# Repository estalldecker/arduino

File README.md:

# arduino
Playing with Arduino platform

Created with [KiCad](http://www.kicad-pcb.org/display/KICAD/KiCad+EDA+Software+Suite) BUILD: (25-Oct-2014 BZR 4029)-stable running in Kubuntu 15.04.

The idea is to implement side turn signals to be used in a bike. We're using for this:
 - 13 leds
 - ATMEGA328P microcontroller 
 - 9 resistors
 - 2 capacitors

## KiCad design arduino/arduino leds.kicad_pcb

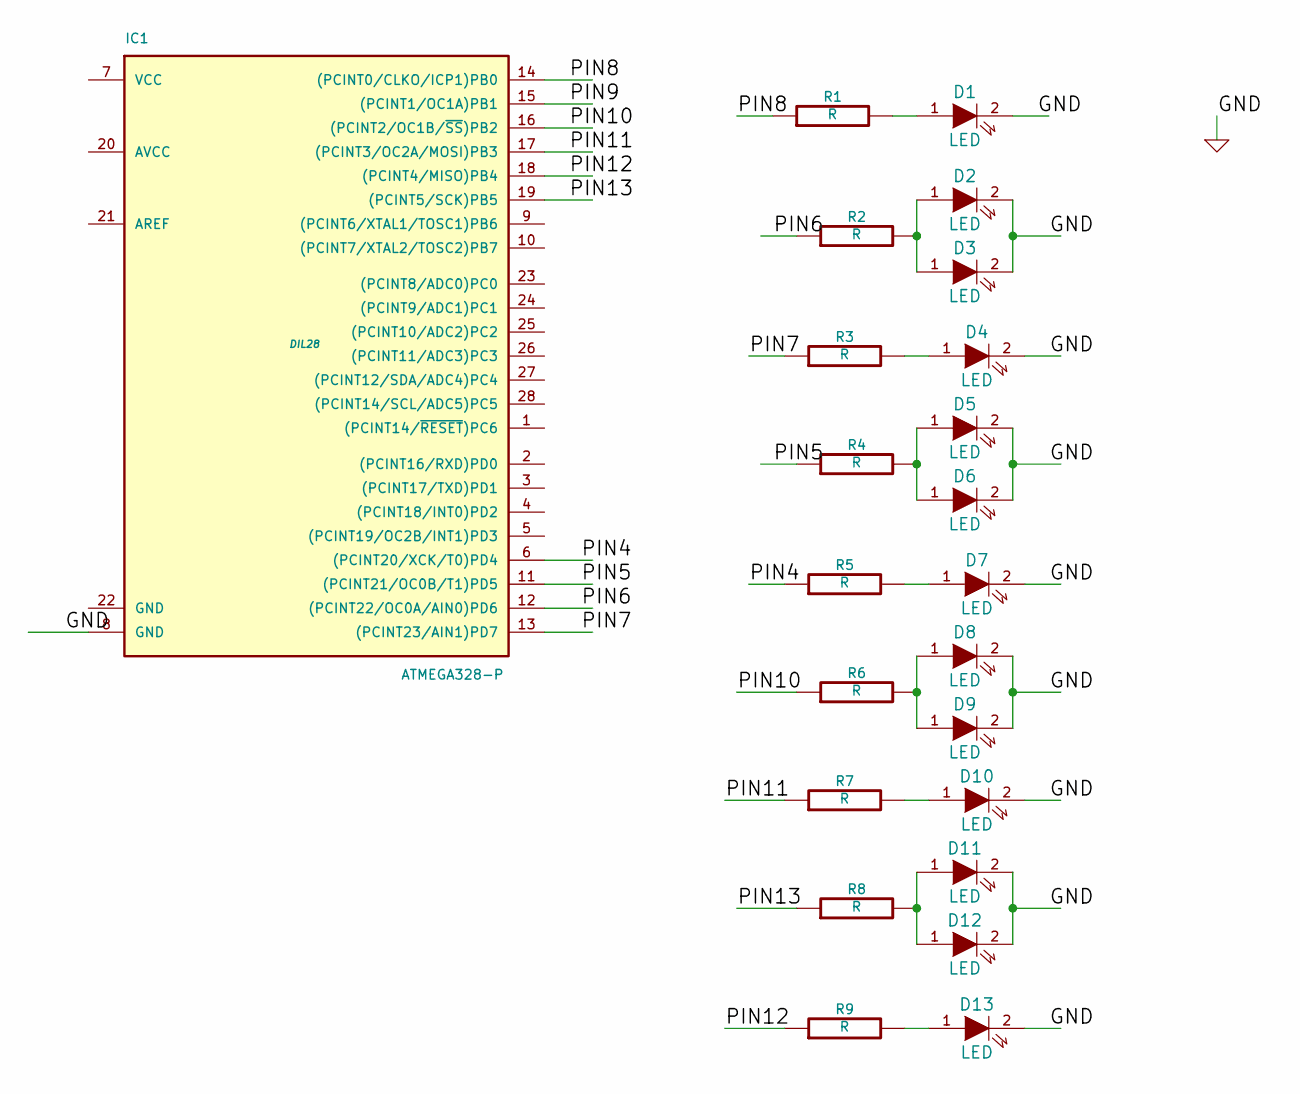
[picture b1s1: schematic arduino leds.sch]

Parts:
D1, D2, D3, D4, D5, D6, D7, D8, D9, D10, D11, D12, D13: LED
IC1: ATMEGA328-P; DIL28
R1, R2, R3, R4, R5, R6, R7, R8, R9: R

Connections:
/PIN4: IC1.6 ((PCINT20/XCK/T0)PD4), R5.1
/PIN5: IC1.11 ((PCINT21/OC0B/T1)PD5), R4.1
/PIN6: IC1.12 ((PCINT22/OC0A/AIN0)PD6), R2.1
/PIN7: IC1.13 ((PCINT23/AIN1)PD7), R3.1
/PIN8: IC1.14 ((PCINT0/CLKO/ICP1)PB0), R1.1
/PIN10: IC1.16 ((PCINT2/OC1B/~SS~)PB2), R6.1
/PIN11: IC1.17 ((PCINT3/OC2A/MOSI)PB3), R7.1
/PIN12: IC1.18 ((PCINT4/MISO)PB4), R9.1
/PIN13: IC1.19 ((PCINT5/SCK)PB5), R8.1
GND: D1.2 (K), D2.2 (K), D3.2 (K), D4.2 (K), D5.2 (K), D6.2 (K), D7.2 (K), D8.2 (K), D9.2 (K), D10.2 (K), D11.2 (K), D12.2 (K), D13.2 (K), IC1.8 (GND)
unnamed: D13.1 (A), R9.2
unnamed: D1.1 (A), R1.2
unnamed: D8.1 (A), D9.1 (A), R6.2
unnamed: D10.1 (A), R7.2
unnamed: D11.1 (A), D12.1 (A), R8.2
unnamed: D4.1 (A), R3.2
unnamed: D7.1 (A), R5.2
unnamed: D5.1 (A), D6.1 (A), R4.2
unnamed: D2.1 (A), D3.1 (A), R2.2

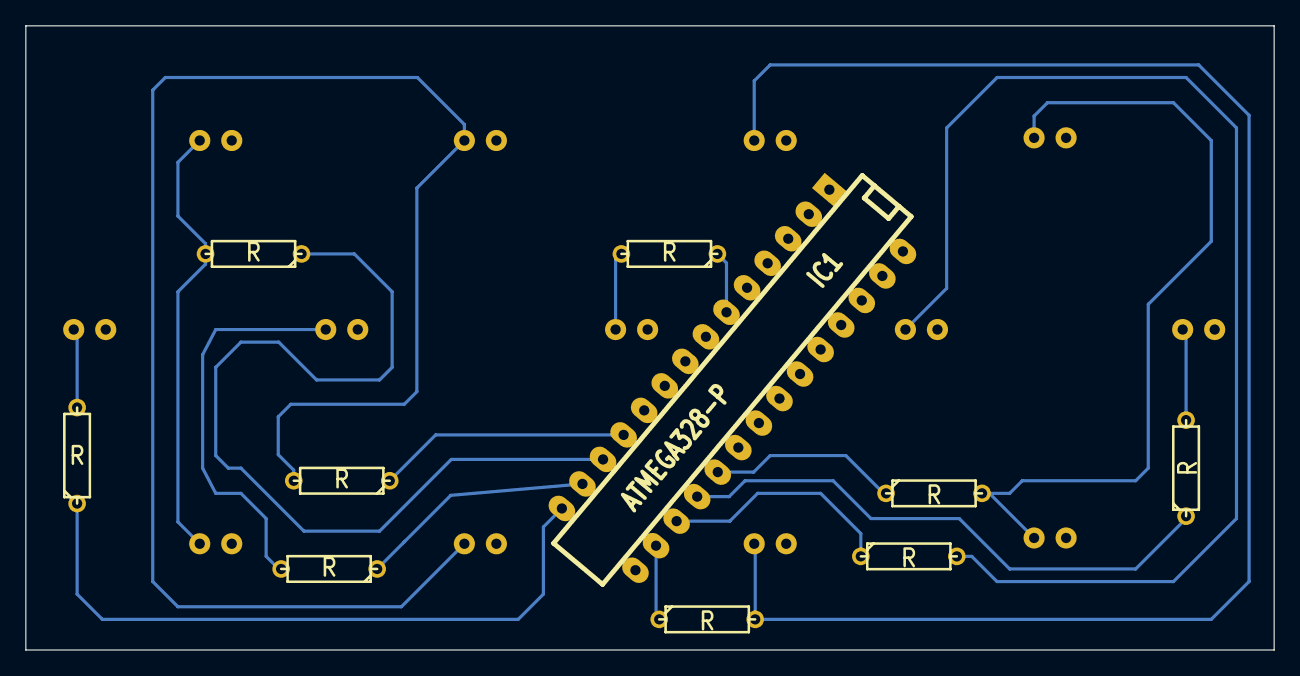
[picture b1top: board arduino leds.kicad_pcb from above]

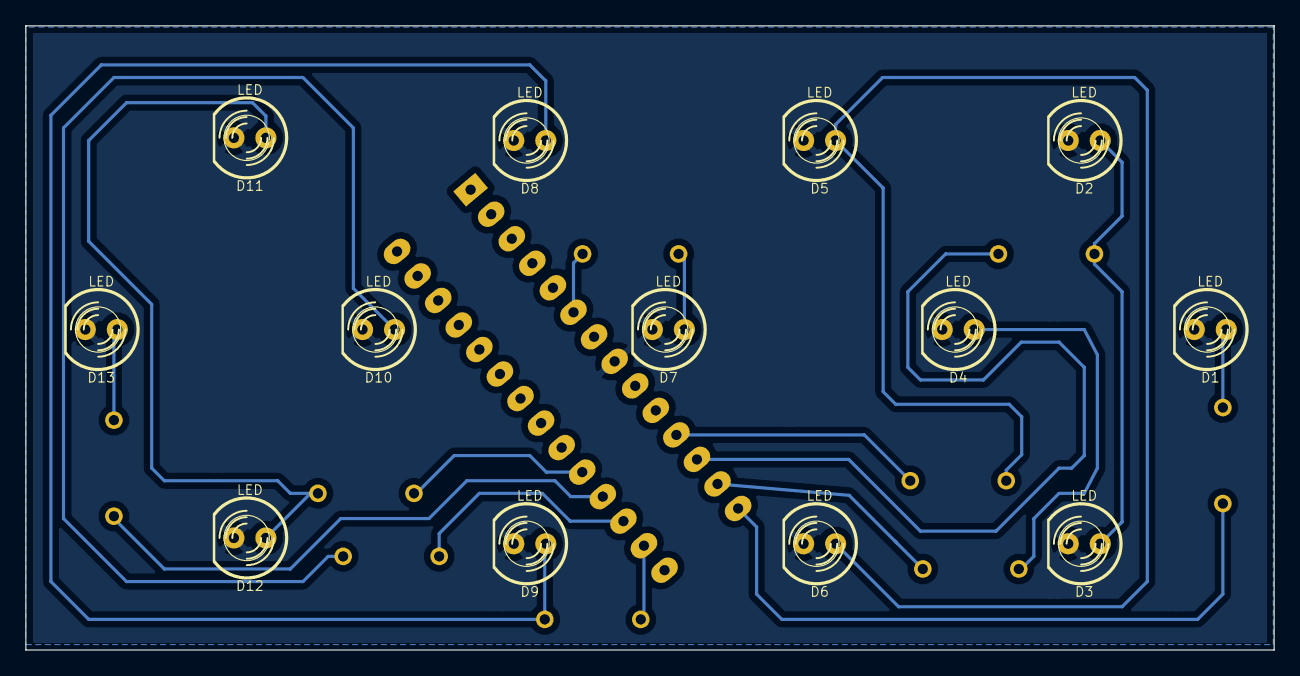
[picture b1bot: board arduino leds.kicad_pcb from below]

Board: 2 copper layers, 99.1 x 49.5 mm, 23 parts (13 on the bottom side), 19 nets.

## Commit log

2015-07-04 Last changes
2015-07-04 images updated
